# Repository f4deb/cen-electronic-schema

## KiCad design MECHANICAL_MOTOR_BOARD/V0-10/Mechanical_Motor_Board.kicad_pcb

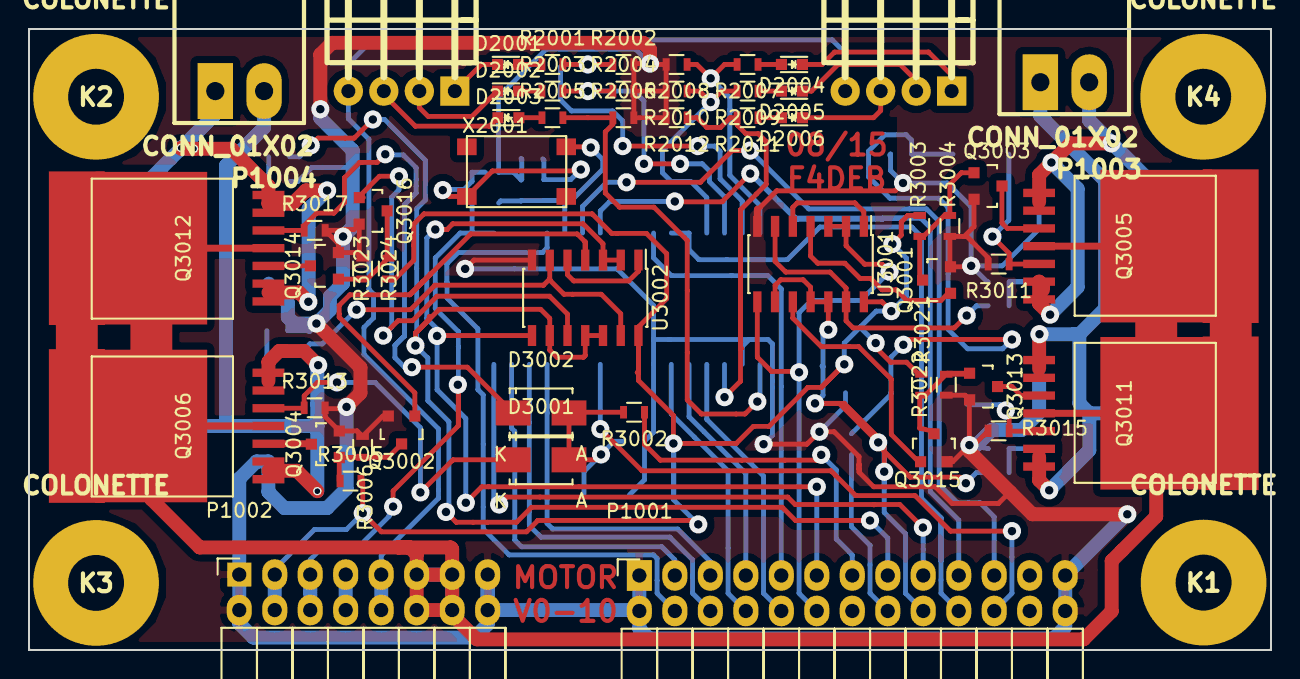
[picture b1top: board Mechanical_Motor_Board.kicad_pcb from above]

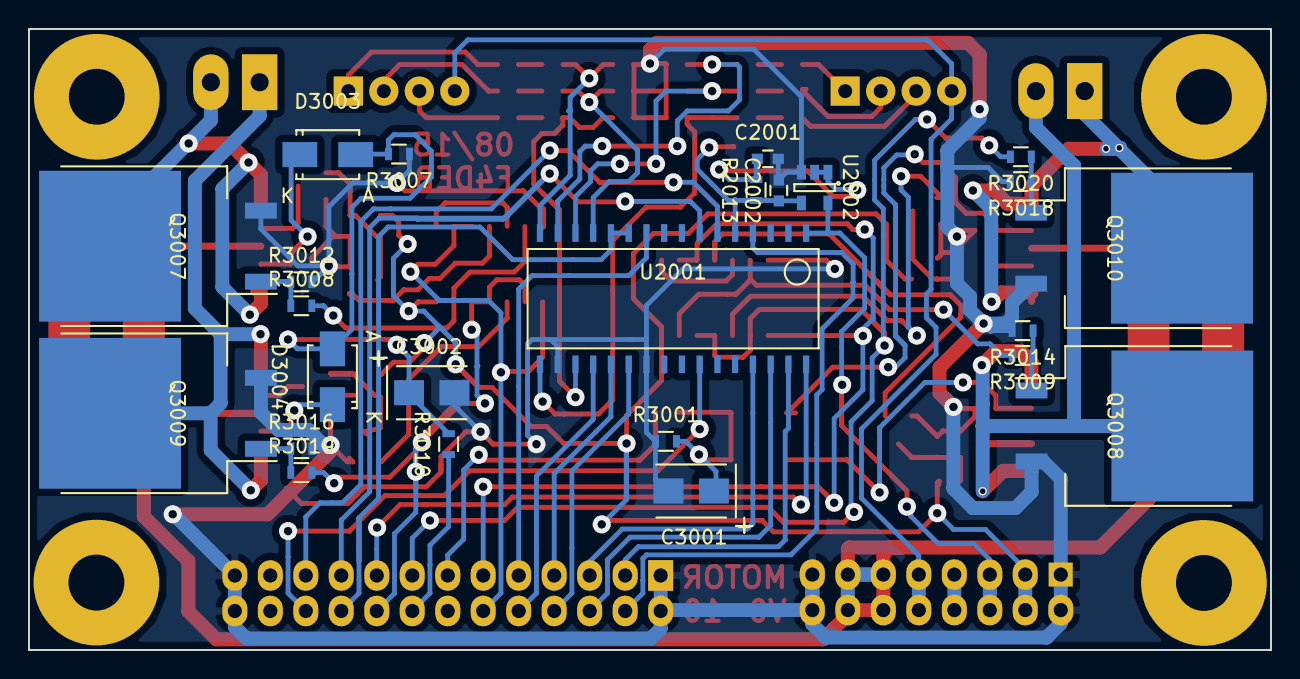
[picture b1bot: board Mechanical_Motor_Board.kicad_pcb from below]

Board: 2 copper layers, 88.9 x 44.5 mm, 82 parts (24 on the bottom side), 75 nets.

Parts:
C2001, C2002: 27p; C_0603
C3001, C3002: C; TantalC_SizeB_EIA-3528_Wave
D2001, D2002, D2003, D2004, D2005, D2006: LED; LED-0603
D3001, D3002, D3003, D3004: D_Schottky_Small; Diode-SMA_Standard
K1, K2, K3, K4: COLONETTE
P1001: CONN_02X13; Socket_Strip_Angled_2x13
P1002: CONN_02X08; Socket_Strip_Angled_2x08
P1003, P1004: CONN_01X02; WEIDMULLER-SL-3.5-2-90G
P1005, P1006: CONN_01X04; KK-4-H
Q3001, Q3002, Q3015, Q3016: 2N7002; SOT-23
Q3003, Q3004, Q3013, Q3014: BSR14; SOT-23
Q3005, Q3006, Q3011, Q3012: BTS50055; PG-TO220-7-4
Q3007, Q3008, Q3009, Q3010: STB80NF55L_06T4; TO-263
R2001, R2002, R2003, R2004, R2005, R2006, R2007, R2008, R2009, R2010, R2011, R2012: 1.5k; R_0603
R2013: 10M; R_0603
R3001, R3002, R3003, R3004, R3005, R3006, R3007, R3008, R3009, R3010, R3011, R3012, R3013, R3014, R3015, R3016, R3017, R3018, R3019, R3020, R3021, R3022, R3023, R3024: R; R_0603
U2001: HCTL-2032; SOJ-32
U2002: M74VHC1GT02DTT1G; SOT-23-5
U3001, U3002: 74HC02; SOIC-14_3.9x8.7mm_Pitch1.27mm
X2001: 12Mhz; MDX75104

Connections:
+3V3: P1002.3, P1002.4, R3003.2, R3005.2, R3021.1, R3023.1, U3001.14, U3002.14
+5V: P1002.7, P1002.8
+5VD: P1002.5, P1002.6, U2001.1, U2002.5
+12V: P1002.9, P1002.10, P1005.4, P1006.4
+15V: P1002.11, P1002.12, P1002.13, P1002.14, Q3005.4, Q3006.4, Q3011.4, Q3012.4
/Codeur/CHAx: D2001.1, P1005.1
/Codeur/CHAy: D2004.1, P1006.1
/Codeur/CHBx: D2002.1, P1005.2
/Codeur/CHBy: D2005.1, P1006.2
/Codeur/CHIx: D2003.1, P1005.3
/Codeur/CHIy: D2006.1, P1006.3
/Codeur/IO1: P1001.21, U2001.6
/Codeur/IO2: P1001.22, U2001.26
/Codeur/IO3: P1001.19, U2001.7
/Codeur/IO4: P1001.20, U2001.11, U2001.12
/Codeur/IO5: P1001.17, U2001.32
/Codeur/IO18: P1001.4, U2001.4
/Codeur/IO19: P1001.3, U2001.31
/Codeur/IO20: P1001.6, U2001.30
/Codeur/IO21: P1001.5, U2001.29
/Codeur/IO22: P1001.8, U2001.22
/Codeur/IO23: P1001.7, U2001.21
/Codeur/IO24: P1001.10, U2001.20
/Codeur/IO25: P1001.9, U2001.10
/Motor/IMOT1: P1001.16, R3010.1
/Motor/IMOT1A: D3003.1, Q3005.5, R3011.1
/Motor/IMOT1B: D3004.1, Q3011.5, R3015.1
/Motor/IMOT2: P1001.13, R3002.1
/Motor/IMOT2A: D3001.1, Q3006.5, R3013.1
/Motor/IMOT2B: D3002.1, Q3012.5, R3017.1
/Motor/IO6: P1001.18, R3019.2, U3001.9, U3001.11, U3001.12
/Motor/IO7: P1001.15, R3020.2, U3002.9, U3002.11, U3002.12
/Motor/M1A: P1003.2, Q3005.1, Q3005.2, Q3005.6, Q3005.7, Q3007.2
/Motor/M1B: P1003.1, Q3009.2, Q3011.1, Q3011.2, Q3011.6, Q3011.7
/Motor/M2A: P1004.2, Q3006.1, Q3006.2, Q3006.6, Q3006.7, Q3008.2
/Motor/M2B: P1004.1, Q3010.2, Q3012.1, Q3012.2, Q3012.6, Q3012.7
/Motor/OC4-5V: P1001.11, U3002.2, U3002.3, U3002.8
/Motor/OC5-5V: P1001.12, U3001.2, U3001.3, U3001.8
GND: C2001.2, C2002.2, C3001.2, C3002.2, P1001.1, P1001.2, P1001.25, P1001.26, P1002.1, P1002.2, P1002.15, P1002.16, Q3001.2, Q3002.2, Q3003.2, Q3004.2, Q3007.3, Q3008.3, Q3009.3, Q3010.3, Q3013.2, Q3014.2, Q3015.2, Q3016.2, R2002.2, R2004.2, R2006.2, R2008.2, R2010.2, R2012.2, R3001.1, R3004.1, R3006.1, R3007.1, R3011.2, R3012.2, R3013.2, R3014.2, R3015.2, R3016.2, R3017.2, R3018.2, R3022.1, R3024.1, U2001.18, U2001.23, U2002.3, U3001.7, U3002.7
unnamed: C2001.1, R2013.2, U2002.1, U2002.2, X2001.1
unnamed: C2002.1, R2013.1, U2001.5, U2002.4, X2001.2
unnamed: C3001.1, D3001.2, D3002.2, R3001.2, R3002.2
unnamed: C3002.1, D3003.2, D3004.2, R3007.2, R3010.2
unnamed: D2001.2, R2001.1
unnamed: D2002.2, R2003.1
unnamed: D2003.2, R2005.1
unnamed: D2004.2, R2007.1
unnamed: D2005.2, R2009.1
unnamed: D2006.2, R2011.1
unnamed: Q3001.1, U3001.4
unnamed: Q3001.3, Q3003.1, R3003.1, R3004.2
unnamed: Q3002.1, U3002.4
unnamed: Q3002.3, Q3004.1, R3005.1, R3006.2
unnamed: Q3003.3, Q3005.3
unnamed: Q3004.3, Q3006.3
unnamed: Q3007.1, R3008.1, R3012.1
unnamed: Q3008.1, R3009.1, R3014.1
unnamed: Q3009.1, R3016.1, R3019.1
unnamed: Q3010.1, R3018.1, R3020.1
unnamed: Q3011.3, Q3013.3
unnamed: Q3012.3, Q3014.3
unnamed: Q3013.1, Q3015.3, R3021.2, R3022.2
unnamed: Q3014.1, Q3016.3, R3023.2, R3024.2
unnamed: Q3015.1, U3001.10
unnamed: Q3016.1, U3002.10
unnamed: R2001.2, R2002.1, U2001.15
unnamed: R2003.2, R2004.1, U2001.14
unnamed: R2005.2, R2006.1, U2001.17
unnamed: R2007.2, R2008.1, U2001.16
unnamed: R2009.2, R2010.1, U2001.13
unnamed: R2011.2, R2012.1, U2001.19
unnamed: R3008.2, U3001.6, U3001.13
unnamed: R3009.2, U3002.6, U3002.13
unnamed: U3001.1, U3001.5
unnamed: U3002.1, U3002.5

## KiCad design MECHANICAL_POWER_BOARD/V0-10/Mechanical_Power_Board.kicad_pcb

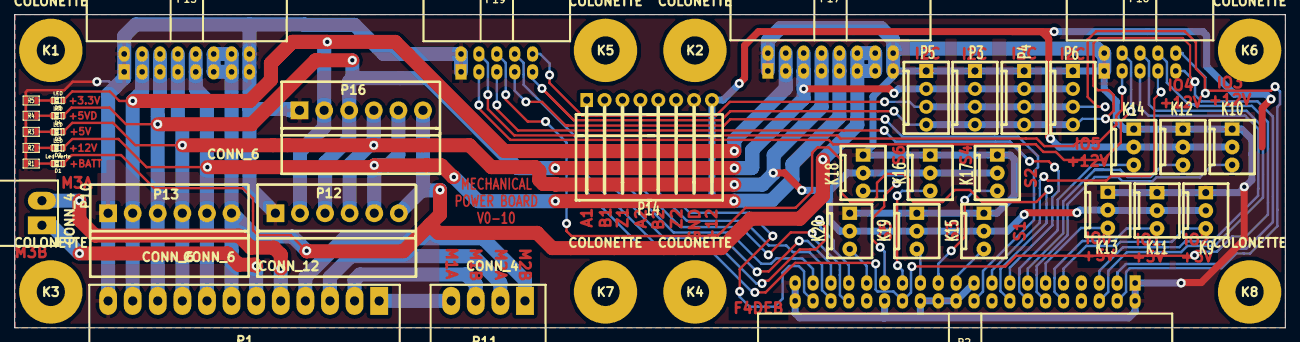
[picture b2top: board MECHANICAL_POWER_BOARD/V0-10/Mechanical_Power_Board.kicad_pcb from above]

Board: 2 copper layers, 180.4 x 44.5 mm, 46 parts (0 on the bottom side), 46 nets.

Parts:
D1: Led Verte; LED-0603
D2, D3, D4, D5: LED; LED-0603
K1, K2, K3, K4, K5, K6, K7, K8: COLONETTE
K9, K10, K11, K12, K13, K14, K15, K16, K17, K18, K19, K20: CONN_3; KK-3
P1: CONN_12; WEIDMULLER-SL-3.5-12-90G
P2: HE10-40; vasch_strip_20x2_90
P3, P4, P5, P6: CONN_4; KK-4
P10: CONN_4; WEIDMULLER-SL-3.5-2-90G
P11: CONN_4; WEIDMULLER-SL-3.5-4-90G
P12, P16: CONN_6; WEIDMULLER6
P13: CONN_6; WEIDMULLER-6
P14: CONN_8; KK-8-H
P15, P17: CONN_8X2; vasch_strip_8x2_90
P18, P19: CONN_5X2; vasch_strip_5x2_90
R1: 1K; SM0603_Resistor
R2: 820; SM0603_Resistor
R3: 680; SM0603_Resistor
R4: 330; SM0603_Resistor
R5: 220; SM0603_Resistor

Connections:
+3.3V: D5.1, P1.11, P12.2, P13.2, P15.3, P15.4, P16.2, P17.3, P17.4
+5V: D3.1, K9.2, K11.2, K13.2, K15.2, K16.2, K17.2, K18.2, K19.2, K20.2, P1.9, P12.4, P13.4, P15.7, P15.8, P16.4, P17.7, P17.8
+5VD: D4.1, P1.10, P3.2, P4.2, P5.2, P6.2, P12.3, P13.3, P15.5, P15.6, P16.3, P17.5, P17.6
+12V: D2.1, K10.2, K12.2, K14.2, P1.8, P12.5, P13.5, P14.8, P15.9, P15.10, P16.5, P17.9, P17.10
+15V: D1.1, P1.7, P12.6, P13.6, P15.11, P15.12, P15.13, P15.14, P16.6, P17.11, P17.12, P17.13, P17.14
/A1: P2.33, P14.1
/A2: P2.34, P14.4
/B1: P2.35, P14.2
/B2: P2.36, P14.5
/IO0: K9.3, P2.9
/IO1: K11.3, P2.10
/IO2: K13.3, P2.11
/IO3: K10.3, P2.12
/IO4: K12.3, P2.13
/IO5: K14.3, P2.14
/IRQ0: P2.17, P18.7
/IRQ2: P2.20, P19.7
/M1A: P1.1, P11.4
/M1B: P1.2, P11.3
/M2A: P1.3, P11.2
/M2B: P1.4, P11.1
/M3A: P1.5, P10.2
/M3B: P1.6, P10.1
/RST: P2.28, P18.8, P19.8
/RX1: P2.5, P18.5
/RX2: P2.15, P19.5
/RX3: P18.4, P19.3
/SCL: P2.4, P3.3, P4.3, P5.3, P6.3, P18.10, P19.10
/SDA: P2.3, P3.4, P4.4, P5.4, P6.4, P18.9, P19.9
/SERV1: K15.3, P2.21
/SERV2: K17.3, P2.23
/SERV3: K19.3, P2.25
/SERV4: K16.3, P2.27
/SERV5: K18.3, P2.29
/SERV6: K20.3, P2.31
/TX1: P2.6, P18.6
/TX2: P2.16, P19.6
/TX3: P18.3, P19.4
/Z1: P2.37, P14.3
/Z2: P2.38, P14.6
GND: K9.1, K10.1, K11.1, K12.1, K13.1, K14.1, K15.1, K16.1, K17.1, K18.1, K19.1, K20.1, P1.12, P2.1, P2.2, P2.19, P2.22, P2.24, P2.26, P2.30, P2.39, P2.40, P3.1, P4.1, P5.1, P6.1, P12.1, P13.1, P14.7, P15.1, P15.2, P15.15, P15.16, P16.1, P17.1, P17.2, P17.15, P17.16, P18.1, P18.2, P19.1, P19.2, R1.1, R2.1, R3.1, R4.1, R5.1
unnamed: D1.2, R1.2
unnamed: D3.2, R3.2
unnamed: D4.2, R4.2
unnamed: D2.2, R2.2
unnamed: D5.2, R5.2

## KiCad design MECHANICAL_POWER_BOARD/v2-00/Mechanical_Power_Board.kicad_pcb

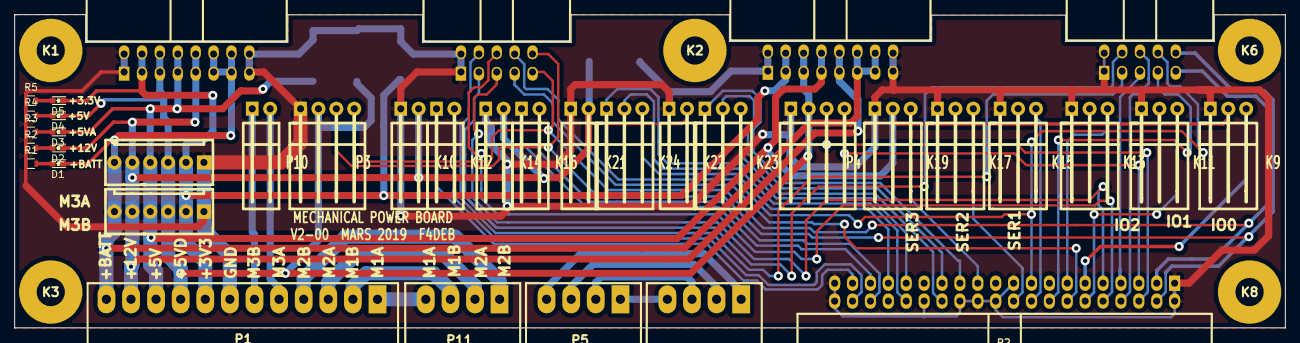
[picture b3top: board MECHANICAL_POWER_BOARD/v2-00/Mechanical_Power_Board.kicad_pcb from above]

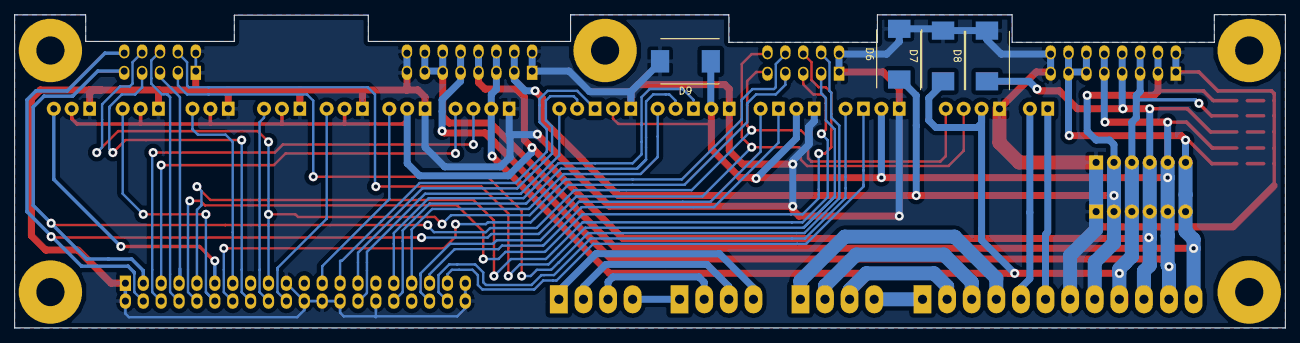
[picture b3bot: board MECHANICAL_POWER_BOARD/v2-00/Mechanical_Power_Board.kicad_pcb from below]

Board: 2 copper layers, 180.4 x 44.5 mm, 47 parts (4 on the bottom side), 50 nets.

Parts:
D1: Led Verte; LED_0603
D2, D3, D4, D5: LED; LED_0603
D6: 3V6; DO-214AB
D7, D8: 5V6; DO-214AB
D9: 13V; DO-214AB
K1, K2, K3, K6, K8: COLONETTE
K9, K11, K13, K15, K17, K19, K23, K24: CONN_3; KK-3-H
K10, K12, K14, K16, K21, K22: CONN_2; KK-2-H
P1: CONN_12; WEIDMULLER-SL-3.5-12-90G
P2: HE10-40; vasch_strip_20x2_90
P3, P4: CONN_4; KK-4-H
P5, P6, P11: CONN_4; WEIDMULLER-SL-3.5-4-90G
P10: CONN_4; KK-2-H
P12, P13: CONN_6; KK-6
P15, P17: CONN_8X2; vasch_strip_8x2_90
P18, P19: CONN_5X2; vasch_strip_5x2_90
R1, R2: 4.7k; R_0603
R3, R4: 1.5k; R_0603
R5: 680; R_0603

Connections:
+3V3: D5.1, D6.1, P1.8, P12.2, P13.2, P15.3, P15.4, P17.3, P17.4
+5V: D3.1, D8.1, K9.2, K11.2, K13.2, K15.2, K17.2, K19.2, P1.10, P12.4, P13.4, P15.7, P15.8, P17.7, P17.8
+5VD: D4.1, D7.1, P1.9, P3.2, P4.2, P12.3, P13.3, P15.5, P15.6, P17.5, P17.6
+12V: D2.1, D9.1, K10.2, K14.2, K21.2, K22.2, P1.11, P12.5, P13.5, P15.9, P15.10, P17.9, P17.10
+15V: D1.1, P1.12, P12.6, P13.6, P15.11, P15.12, P15.13, P15.14, P17.11, P17.12, P17.13, P17.14
/A1: K23.1, P2.25
/A2: K24.1, P2.31
/A3: K16.1, P2.35
/A4: K12.1, P2.37
/B1: K23.2, P2.27
/B2: K24.2, P2.32
/B3: K16.2, P2.36
/B4: K12.2, P2.38
/IO0: K9.3, P2.11
/IO1: K11.3, P2.12
/IO2: K13.3, P2.13
/IRQ0: P2.16, P18.7
/IRQ2: P2.14, P19.7
/M1A: P1.1, P11.4
/M1B: P1.2, P11.3
/M2A: P1.3, P11.2
/M2B: P1.4, P11.1
/M3A: P1.5, P10.2
/M3B: P1.6, P10.1
/M4A: P5.4, P6.1
/M4B: P5.3, P6.2
/M5A: P5.2, P6.3
/M5B: P5.1, P6.4
/RST: P2.17, P18.8, P19.8
/RX1: P2.7, P18.5
/RX2: P2.9, P19.5
/RX3: P18.4, P19.3
/SCL1: P2.4, P3.3, P18.10, P19.10
/SCL4: P2.6, P4.3
/SDA1: P2.3, P3.4, P18.9, P19.9
/SDA4: P2.5, P4.4
/SERV1: K15.3, P2.18
/SERV2: K17.3, P2.20
/SERV3: K19.3, P2.23
/TX1: P2.8, P18.6
/TX2: P2.10, P19.6
/TX3: P18.3, P19.4
/Z1: K23.3, P2.28
/Z2: K24.3, P2.33
GND: D6.2, D7.2, D8.2, D9.2, K9.1, K10.1, K11.1, K13.1, K14.1, K15.1, K17.1, K19.1, K21.1, K22.1, P1.7, P2.1, P2.2, P2.19, P2.22, P2.24, P2.26, P2.30, P2.39, P2.40, P3.1, P4.1, P12.1, P13.1, P15.1, P15.2, P15.15, P15.16, P17.1, P17.2, P17.15, P17.16, P18.1, P18.2, P19.1, P19.2, R1.1, R2.1, R3.1, R4.1, R5.1
unnamed: D1.2, R1.2
unnamed: D2.2, R2.2
unnamed: D3.2, R3.2
unnamed: D4.2, R4.2
unnamed: D5.2, R5.2
